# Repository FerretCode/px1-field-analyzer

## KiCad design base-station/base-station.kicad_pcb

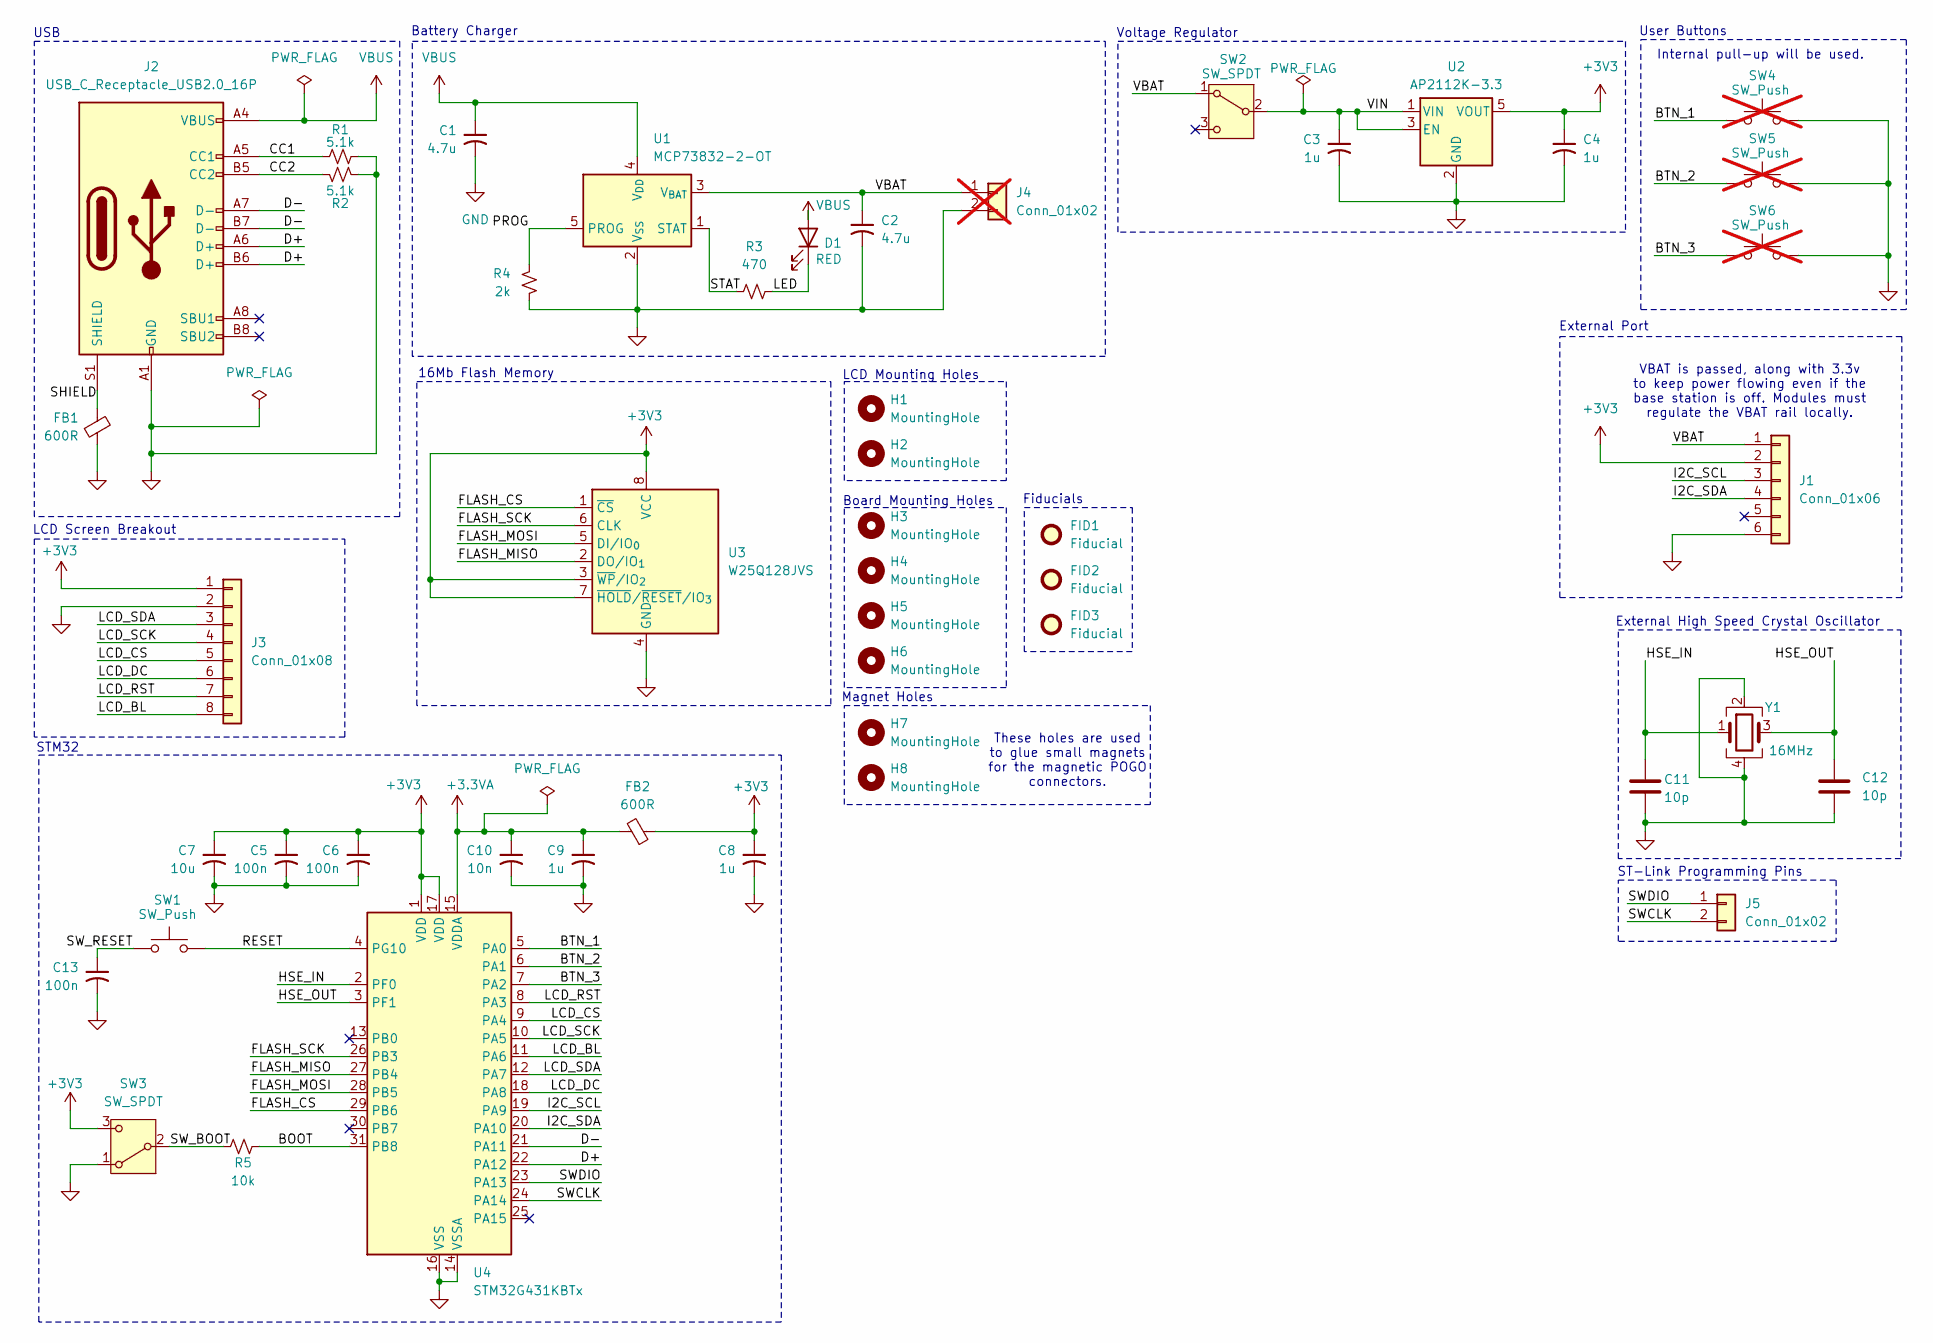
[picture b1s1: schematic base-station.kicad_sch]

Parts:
C1, C2: 4.7u; C_0402_1005Metric; LCSC PN C77004
C3, C4, C8, C9: 1u; C_0402_1005Metric; LCSC PN C14445
C5, C6, C13: 100n; C_0402_1005Metric; LCSC PN C71687
C7: 10u; C_0402_1005Metric; LCSC PN C77000
C10: 10n; C_0402_1005Metric; LCSC PN C541371
C11, C12: 10p; C_0402_1005Metric; LCSC PN C106199
D1: RED; LED_0805_2012Metric; LCSC PN C284871
FB1, FB2: 600R; L_0805_2012Metric; LCSC PN C1017
FID1, FID2, FID3: Fiducial; Fiducial_1mm_Mask3mm
H1, H2: MountingHole; MountingHole_3.5mm
H3, H4, H5, H6: MountingHole; MountingHole_4mm
H7, H8: MountingHole; MountingHole_2.1mm
J1: Conn_01x06; PinHeader_1x06_P2.54mm_Vertical_SMD_Pin1Left
J2: USB_C_Receptacle_USB2.0_16P; USB_C_Receptacle_HRO_TYPE-C-31-M-12; LCSC PN C165948
J3: Conn_01x08; PinHeader_1x08_P2.54mm_Vertical; LCSC PN C190820
J4: Conn_01x02; JST_PH_S2B-PH-K_1x02_P2.00mm_Horizontal; not fitted
J5: Conn_01x02; PinHeader_1x02_P2.54mm_Vertical; LCSC PN C234182
R1, R2: 5.1k; R_0603_1608Metric; LCSC PN C23186
R3: 470; R_0805_2012Metric; LCSC PN C17710
R4: 2k; R_0805_2012Metric; LCSC PN C17604
R5: 10k; R_0805_2012Metric; LCSC PN C17414
SW1: SW_Push; SW_Push_1P1T_NO_CK_KMR2; LCSC PN C221675
SW2, SW3: SW_SPDT; SW_SPDT_PCM12; LCSC PN C431540
SW4, SW5, SW6: SW_Push; Kailh_socket_PG1350_optional; not fitted
U1: MCP73832-2-OT; SOT-23-5; LCSC PN C38066
U2: AP2112K-3.3; SOT-23-5; LCSC PN C23380830
U3: W25Q128JVS; SOIC-8_5.3x5.3mm_P1.27mm; LCSC PN C97521
U4: STM32G431KBTx; LQFP-32_7x7mm_P0.8mm; LCSC PN C529357
Y1: 16MHz; Crystal_SMD_3225-4Pin_3.2x2.5mm; LCSC PN C112972

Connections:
+3.3VA: C9.1, C10.1, FB2.2, U4.15 (VDDA)
+3V3: C4.1, C5.1, C6.1, C7.1, C8.1, FB2.1, J1.2, J3.1, SW3.3 (C), U2.5 (VOUT), U3.3 (~WP/IO_{2}), U3.7 (~HOLD/~RESET/IO_{3}), U3.8 (VCC), U4.1 (VDD), U4.17 (VDD)
/BOOT: R5.2, U4.31 (PB8)
/BTN_1: SW4.2, U4.5 (PA0)
/BTN_2: SW5.2, U4.6 (PA1)
/BTN_3: SW6.2, U4.7 (PA2)
/CC1: J2.A5 (CC1), R1.1
/CC2: J2.B5 (CC2), R2.1
/D+: J2.A6 (D+), J2.B6 (D+), U4.22 (PA12)
/D-: J2.A7 (D-), J2.B7 (D-), U4.21 (PA11)
/FLASH_CS: U3.1 (~CS), U4.29 (PB6)
/FLASH_MISO: U3.2 (DO/IO_{1}), U4.27 (PB4)
/FLASH_MOSI: U3.5 (DI/IO_{0}), U4.28 (PB5)
/FLASH_SCK: U3.6 (CLK), U4.26 (PB3)
/HSE_IN: C11.1, U4.2 (PF0), Y1.1
/HSE_OUT: C12.1, U4.3 (PF1), Y1.3
/I2C_SCL: J1.3, U4.19 (PA9)
/I2C_SDA: J1.4, U4.20 (PA10)
/LCD_BL: J3.8, U4.11 (PA6)
/LCD_CS: J3.5, U4.9 (PA4)
/LCD_DC: J3.6, U4.18 (PA8)
/LCD_RST: J3.7, U4.8 (PA3)
/LCD_SCK: J3.4, U4.10 (PA5)
/LCD_SDA: J3.3, U4.12 (PA7)
/LED: D1.1 (K), R3.2
/PROG: R4.1, U1.5 (PROG)
/RESET: SW1.2, U4.4 (PG10)
/SHIELD: FB1.2, J2.S1 (SHIELD)
/STAT: R3.1, U1.1 (STAT)
/SWCLK: J5.2, U4.24 (PA14)
/SWDIO: J5.1, U4.23 (PA13)
/SW_BOOT: R5.1, SW3.2 (B)
/SW_RESET: C13.1, SW1.1
/VBAT: C2.1, J1.1, J4.1, SW2.1 (A), U1.3 (V_{BAT})
/VIN: C3.1, SW2.2 (B), U2.1 (VIN), U2.3 (EN)
GND: C1.2, C2.2, C3.2, C4.2, C5.2, C6.2, C7.2, C8.2, C9.2, C10.2, C11.2, C12.2, C13.2, FB1.1, J1.6, J2.A1 (GND), J2.A12 (GND), J2.B1 (GND), J2.B12 (GND), J3.2, J4.2, R1.2, R2.2, R4.2, SW3.1 (A), SW4.1, SW5.1, SW6.1, U1.2 (V_{SS}), U2.2 (GND), U3.4 (GND), U4.14 (VSSA), U4.16 (VSS), U4.32 (VSS), Y1.2, Y1.4
VBUS: C1.1, D1.2 (A), J2.A4 (VBUS), J2.A9 (VBUS), J2.B4 (VBUS), J2.B9 (VBUS), U1.4 (V_{DD})

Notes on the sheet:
Magnet Holes
ST-Link Programming Pins
USB
These holes are used to glue small magnets for the magnetic POGO connectors.
Fiducials
LCD Screen Breakout
User Buttons
External Port
Voltage Regulator
16Mb Flash Memory
VBAT is passed, along with 3.3v to keep power flowing even if the base station is off. Modules must regulate the VBAT rail locally.
External High Speed Crystal Oscillator
LCD Mounting Holes
Internal pull-up will be used.
Battery Charger
STM32
Board Mounting Holes

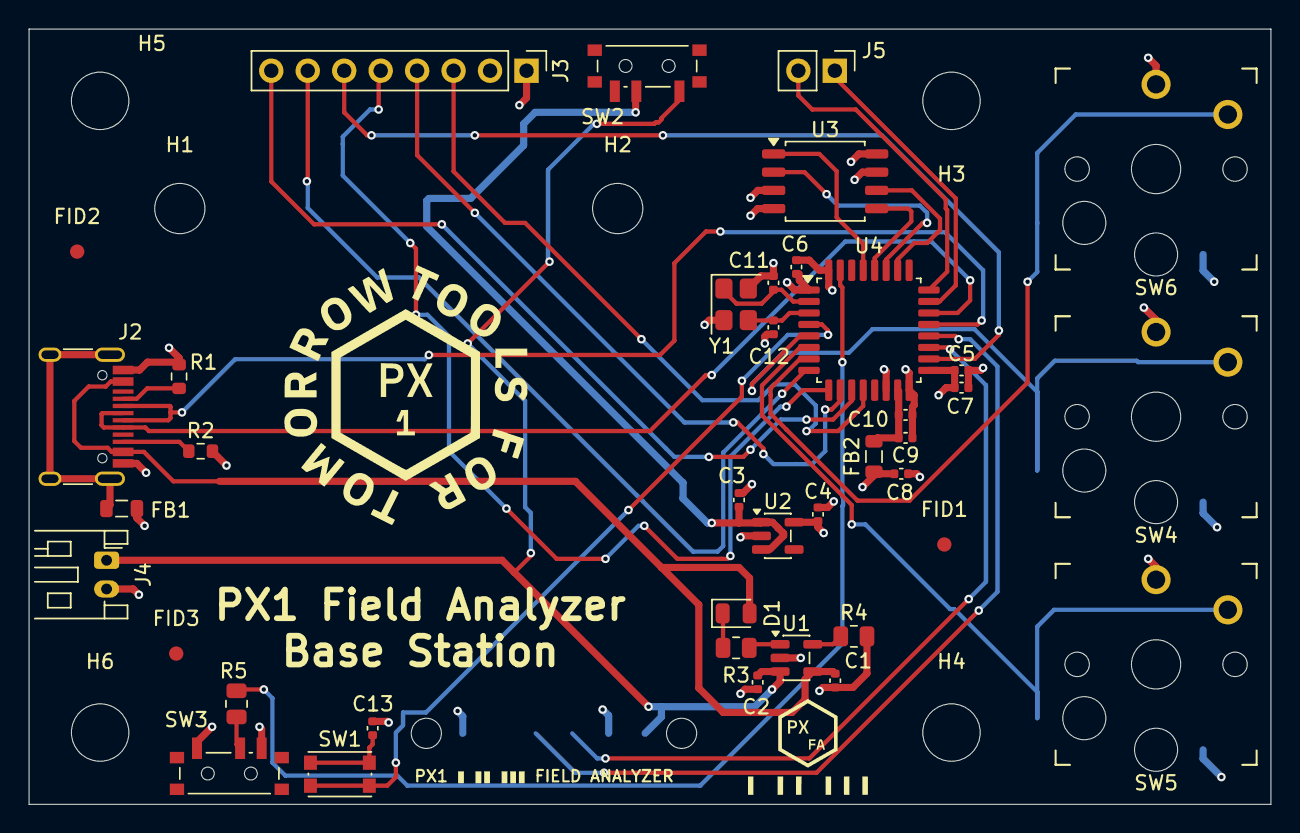
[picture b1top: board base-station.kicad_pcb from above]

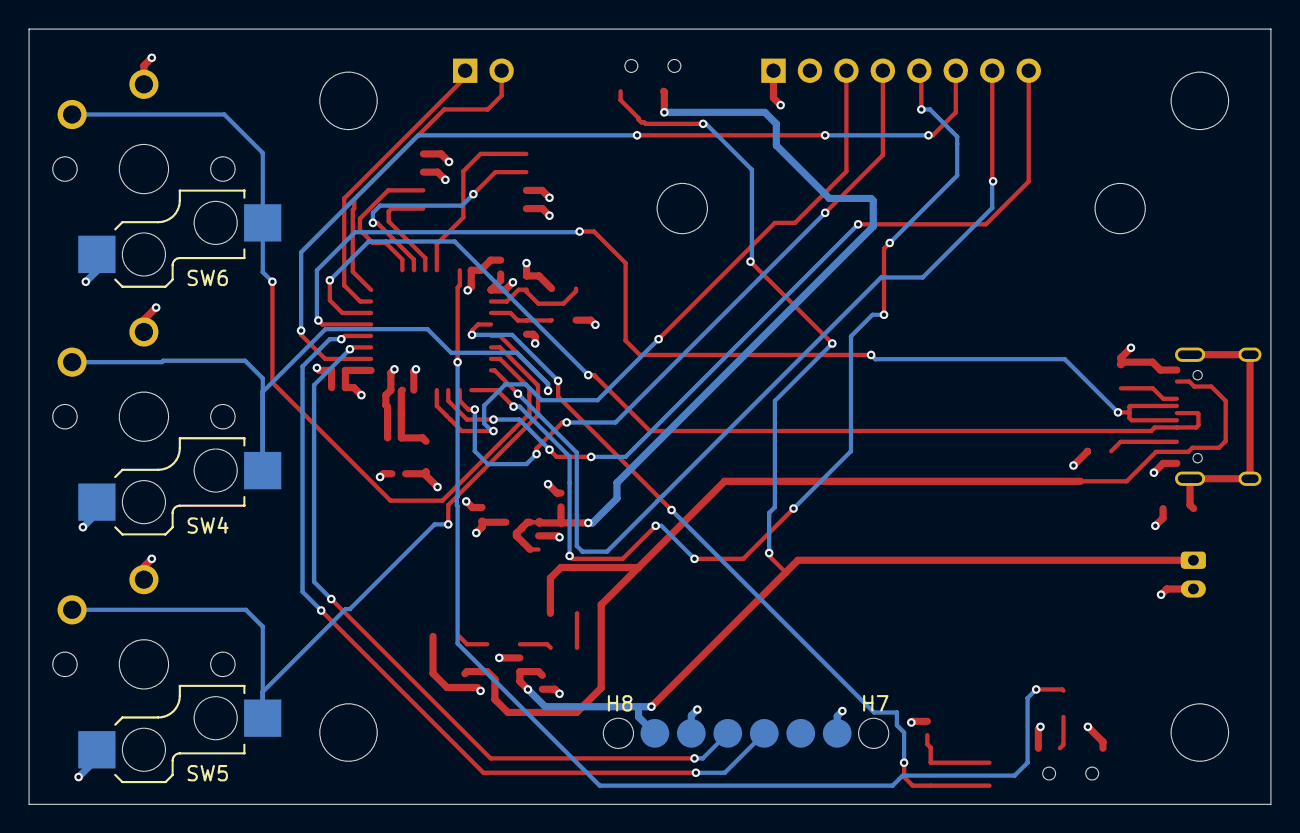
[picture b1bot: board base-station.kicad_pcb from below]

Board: 4 copper layers, 86.5 x 54.0 mm, 48 parts (3 on the bottom side), 37 nets.

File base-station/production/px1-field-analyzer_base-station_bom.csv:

Designator,Footprint,Quantity,Value,LCSC Part #
"C1, C2",0402,2,4.7u,C77004
C10,0402,1,10n,C541371
"C11, C12",0402,2,10p,C106199
"C13, C5, C6",0402,3,100n,C71687
"C3, C4, C8, C9",0402,4,1u,C14445
C7,0402,1,10u,C77000
D1,0805,1,RED,C284871
"FB1, FB2",0805,2,600R,C1017
J1,PinHeader_1x06_P2.54mm_Vertical_SMD_Pin1Left,1,Conn_01x06,
J2,USB_C_Receptacle_HRO_TYPE-C-31-M-12,1,USB_C_Receptacle_USB2.0_16P,C165948
J3,PinHeader_1x08_P2.54mm_Vertical,1,Conn_01x08,C190820
J5,PinHeader_1x02_P2.54mm_Vertical,1,Conn_01x02,C234182
"R1, R2",0603,2,5.1k,C23186
R3,0805,1,470,C17710
R4,0805,1,2k,C17604
R5,0805,1,10k,C17414
SW1,SW_Push_1P1T_NO_CK_KMR2,1,SW_Push,C221675
"SW2, SW3",SW_SPDT_PCM12,2,SW_SPDT,C431540
U1,SOT-23-5,1,MCP73832-2-OT,C38066
U2,SOT-23-5,1,AP2112K-3.3,C23380830
U3,SOIC-8_5.3x5.3mm_P1.27mm,1,W25Q128JVS,C97521
U4,LQFP-32_7x7mm_P0.8mm,1,STM32G431KBTx,C529357
Y1,Crystal_SMD_3225-4Pin_3.2x2.5mm,1,16MHz,C112972

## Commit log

2025-12-12 add base station schematic
2025-12-13 add layout
2025-12-13 add theming
2025-12-14 add mfg files
